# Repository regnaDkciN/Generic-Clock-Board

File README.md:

# Generic Clock Board

An ESP32 based PC board that is specifically designed to support electronic clocks.  Supports the following:
- Adafruit Huzzah32 - ESP32 Feather board for control.
- Optional Adafruit DS3231 Real Time Clock module.
- Optional 5 volt ULN2003 stepper motor driver with optional phase display LEDs (mainly intended for use with a 28BYJ-48 stepper motor).
- Optional home input for homing the stepper motor, if used.  Can be used for other purpose if home is not needed.
- RGB LED for status display.
- Pushbutton input for general clock use.
- Optional 2 auxiliary I/O which can be individually used as inputs or outputs as needed.
- All components are through hole for easy construction.
- Supporting Arduino IDE board driver written in C++.

The motivation for this board was gzumwalt's excellent Geneva Clock which was originally published on printables and cults3d:
[ https://www.printables.com/model/717033-geneva-clock](https://www.printables.com/model/717033-geneva-clock) and
 [https://cults3d.com/en/3d-model/home/geneva-clock](https://cults3d.com/en/3d-model/home/geneva-clock)

---
## Parts List
- 1 Generic Clock Board (files attached).
- 1 [Adafruit Huzzah32-ESP32](https://www.adafruit.com/product/3405).
- 1 **Optional** [Adafruit DS3231 Real Time Clock](https://www.adafruit.com/product/3013).  Used to provide battery backed time in case power is lost or an internet connection cannot be made.
- 1 **Optional**[Right Angle Tactile Pushbutton Switch](https://www.amazon.com/dp/B008DS16PO?psc=1&ref=ppx_yo2ov_dt_b_product_details).  Pushbutton for general clock use.
- 1 **Optional** [ULN2003 High Voltage Driver](https://www.amazon.com/ALLECIN-ULN2003-ULN2003APG-High-Voltage-High-Current/dp/B0CBM23ZJ3/ref=sr_1_5?sr=8-5).  Used to drive a 5 volt stepper motor.
- 1 **Optional** 10nf capacitor.  Used for ULN2003 bypass.
- 4 **Optional** LED (color as desired).  Used to display stepper motor phase selection, which might be useful for debugging stepper.  Otherwise, not really needed.
- 4 **Optional** 10K resistors.  Used only if the optional LEDs are included.
- 1 **Optional** [5 Pin JST XH Male Connector](https://www.amazon.com/dp/B09JP2D9BH?ref=ppx_yo2ov_dt_b_product_details).  Used to connect to the stepper motor, if used.
- 1 **Optional** [5mm RGB LED](https://www.amazon.com/EDGELEC-Tri-Color-Multicolor-Diffused-Resistors/dp/B077XGF3YR/ref=sr_1_5?sr=8-5).  To display general status if desired.
- 3 **Optional** 330 ohm resistors.  Supports RGB LED, if used.
- 1 **Optional** [2-pin JST male connector](https://www.amazon.com/daier-Micro-2-Pin-Connector-Female/dp/B01DUC1O68/ref=sr_1_9?sr=8-9).  Used for home sensor connector.
- 1 **Optional** [4-pin JST male connector](https://www.amazon.com/Sets-2-5-4-Connector-200mm-Female/dp/B01DUC1S14/ref=sr_1_4?sr=8-4).  For the optional auxiliary connector.

---

## Generic Clock Board Library

The included interface library provides convenient use of the basic elements of the board.  Interfaces exist for the stepper, LEDs, home sensor, and pushbutton switch.  The library consists of the following files:
- GenericClockBoard.h - Declares the GenericClockBoard class.
- GenericClockBoard.cpp - Contains the GenericClockBoard class method implementation.
- SerialDebugSetup.h - Selects compile time options for the SerialDebug library which is used to generate serial test and debug output for the library.

The GenericClockBoard library requires the following libraries to be installed in the Arduino IDE:
- [RGBLed Library](https://github.com/wilmouths/RGBLed): This library supports the board's RGB LEDs and provides dimming and color mixing support.
- [SerialDebug Library](https://github.com/JoaoLopesF/SerialDebug ): This library supports serial debugging and status display.

## StepperSpeed_t enum
This enum is used to select the speed profile that will be used for stepper movement via the Step() method.  Selections are:
- *__StepSlow__* - Will move the stepper at slow speed for the full duration of the move.
- *__StepAuto__* - Will make long moves use the fast speed with accel and decel at the beginning and end of the move.  Short moves will be done at slow speed.
- *__StepFast__* - Will move the stepper at fast speed for the full duration of the move.

## Generic Clock Board Library API
### Constructor
Constructs a class instance, initializes board hardware, and initializes instance variables.
#### Constructor Arguments:
 - *__rapidSecondsPerRev__*  - (uint32_t) Specifies the number of seconds it takes the stepper to make one full revolution of its output shaft.  For the 28BYJ-48 stepper motor, a good range is normally between 6 and 10 seconds.
- *__fullStepsPerRev__* - (uint32_t) Specifies the number of FULL steps per revolution of the stepper motor's output shaft.  For the   28BYJ-48 the value is 2048.
- *__stepperPinsReversed__* - (bool) Specifies the whether or not the stepper turns clockwise when a positive step value is commanded.  Set to 'true' if a positive step value causes counterclockwise movement.  Set to 'false' otherwise.
- *__stepperHalfStepping__* - (bool) Specifies whether half stepping is to be used.  If 'true', then half stepping is used, which will cause the number of steps per rev of the stepper to double.  For example, the 28BYJ-48 stepper will take 4096 steps per rev if this value is set to 'true'.  In most cases, use of half stepping is a good choice.
- *__homeNormallyOpen__* - (bool) Specifies the type of sensor used for homing the clock.  Set to 'true' for normally open  (N.O.) sensors.  Set to 'false' for normally closed (N.C.) sensors.

#### Constructor Example
```
// RAPID_SECONDS_PER_REV specifies the number of seconds it takes for the stepper
// motor to complete 1 full revolution at its maximum speed.  A good value for
// the 28BYJ-48 stepper motor is usually in the range of 6 to 10 seconds.
const uint32_t RAPID_SECONDS_PER_REV = 8;

// 28BYJ-48 has 2048 full steps per full rev of the output shaft (4096 half steps).
const uint32_t FULL_STEPS_PER_REV = 2048;

// This stepper needs to have the phases reversed.  Set to 'false' if stepper runs
// backwards.
const bool REVERSE_STEPPER = true;

// USE_HALF_STEPPING selects the use of half stepping of the stepper motor.
// Half stepping is recommended, and is specified by setting this constant to
// ture.  If full stepping is desired, set it to false.
const bool USE_HALF_STEPPING = true;

// The home sensor is normally open.  Set to false if normally closed.
const bool HOME_SWITCH_NORMALLY_OPEN = true;

GenericClockBoard gClock(RAPID_SECONDS_PER_REV, FULL_STEPS_PER_REV,  
                         REVERSE_STEPPER, USE_HALF_STEPPING, HOME_SWITCH_NORMALLY_OPEN);
```

### Step()
Step the stepper motor a specific number of steps in a specified direction at a specified speed.
#### Step() Arguments
- *__steps__* - (int32_t) Specifies the number of steps and direction that the motor will move.  A positive value will move the motor in the clockwise (CW) direction.  A negative value will move the motor in the counterclockwise (CCW) direction.
- *__speed__* - (StepperSpeed_t) Specifies the speed profile that will be used for the move.  StepSlow selects slow stepper speed.  StepAuto selects automatic stepper speed with accel and decel.  StepFast selects fast stepper speed.
#### Step() Example
```
	// Move the stepper 100 steps CW with the Auto profile.
	gClock.Step(100, StepAuto);
```
---
### IsHome()
Returns 'true' if the home sensor is active, based on the type of sensor (N.O. or N.C.) in use.  Returns 'false' otherwise.

#### IsHome() Example
```
	// Move the stepper slowly CW until home is found.
	while (!gClock.IsHome()
	{
		gClock.Step(1, StepSlow);
	}
```
---

### IsButtonPressed()
Returns 'true' if the board's pushbutton is active.  Returns 'false' otherwise.

#### IsButtonPressed() Example
```
	// Set the RGB LED to magenta if the button is pressed.
	if (gClock.IsButtonPressed())
	{
		gClock.RgbLed.brightness(RGBLed::MAGENTA, 2);
	}
```
---
### GenericClockBoard Public Data

#### RGB LED
The RGB LED is normally controlled via an instance of the RGBLed class that is created in the GenericClockBoard constructor.  The RGBLed instance is defined as:
```
    // RGBLed instance (public for easy access).
    static RGBLed RgbLed;
```
See the [RGBLed library documentation](https://github.com/wilmouths/RGBLed) for details on use.  An example of RgbLed is:
```
	// Set the RGB LED color to red with a brightness of 2.
	gClock.RgbLed.brightness(RGBLed::RED, 2);
```
The I/O pin assignments for the RGB LED are exposed as public constants, and may be used to control the LED if needed, but normally the RgbLed member should be used.  The LED pin assignments are defined as:
```
    static const uint8_t LED_RED_PIN   = 13;  // Red LED output pin assignment.
    static const uint8_t LED_GREEN_PIN = 12;  // Green LED output pin assignment.
    static const uint8_t LED_BLUE_PIN  = 27;  // Blue LED output pin assignment.
```
---

#### Auxiliary I/O Pin Assignments
The auxiliary I/O pin assignments are exposed for public use as follows:
```
    static const uint8_t AUX_1_PIN      = 15;  // Aux1 I/O pin assignment.
    static const uint8_t AUX_2_PIN      = 33;  // Aux2 I/O pin assignment.
```  
 These pins are not initialized or used in any way by the GenericClockBoard class, and can be used as desired.
 
---

#### Stepper Motor Direction Constants

The following constants may be used with the Step() method to assist in commanding the direction of stepper movement:
```
    static const int32_t STEP_CW        = 1;   // Clockwise specifier.
    static const int32_t STEP_CCW       = -1;  // Counterclockwise specifier.

```

An example of the use of these constants is:
```
	// Move 5 steps in the CCW direction.
	gClock.Step(STEP_CCW * 5, StepAuto);
```
---

### Private Constants
Several private constants may be of interest to users who do not want to use the provided GenericClockBoard code.  These constants identify the remainder of the I/O pins used by the board.
```
    // Stepper related constants.
    static const uint8_t PHASE_1_PIN = 19;
    static const uint8_t PHASE_2_PIN = 16;
    static const uint8_t PHASE_3_PIN = 17;
    static const uint8_t PHASE_4_PIN = 21;

    // I/O pin assignments.
    static const uint8_t HOME_PIN       = 32;   // Home input pin assignment.
    static const uint8_t PUSHBUTTON_PIN = 26;   // Pushbutton input pin assignment.

```
---

## General Notes
Interface to the ESP32 WiFi is left to the user.  The prototype code uses the 
[WiFiTimeManager library](https://github.com/regnaDkciN/WiFiTimeManager) for WiFi and DST management.  Similarly, interface to the DS3231 RTC is left to the user.  The prototype code uses the [DS323x_Generic Library](https://github.com/khoih-prog/DS323x_Generic) for RTC interface.

An example of using the full features of this board, including WiFi, DST management, RTC, RGB LEDs, and all other hardware can be found at [my GenevaClock git site](https://github.com/regnaDkciN/GenevaClock).

Next revision (if any) may include:
- Add an input for higher voltage ULN3003 feed for more capable stepper capability.
- Tie Home input and Selector Switch input to +5 volts instead of ground so that ESP32 internal pulldowns can be used to eliminate inversion in code.

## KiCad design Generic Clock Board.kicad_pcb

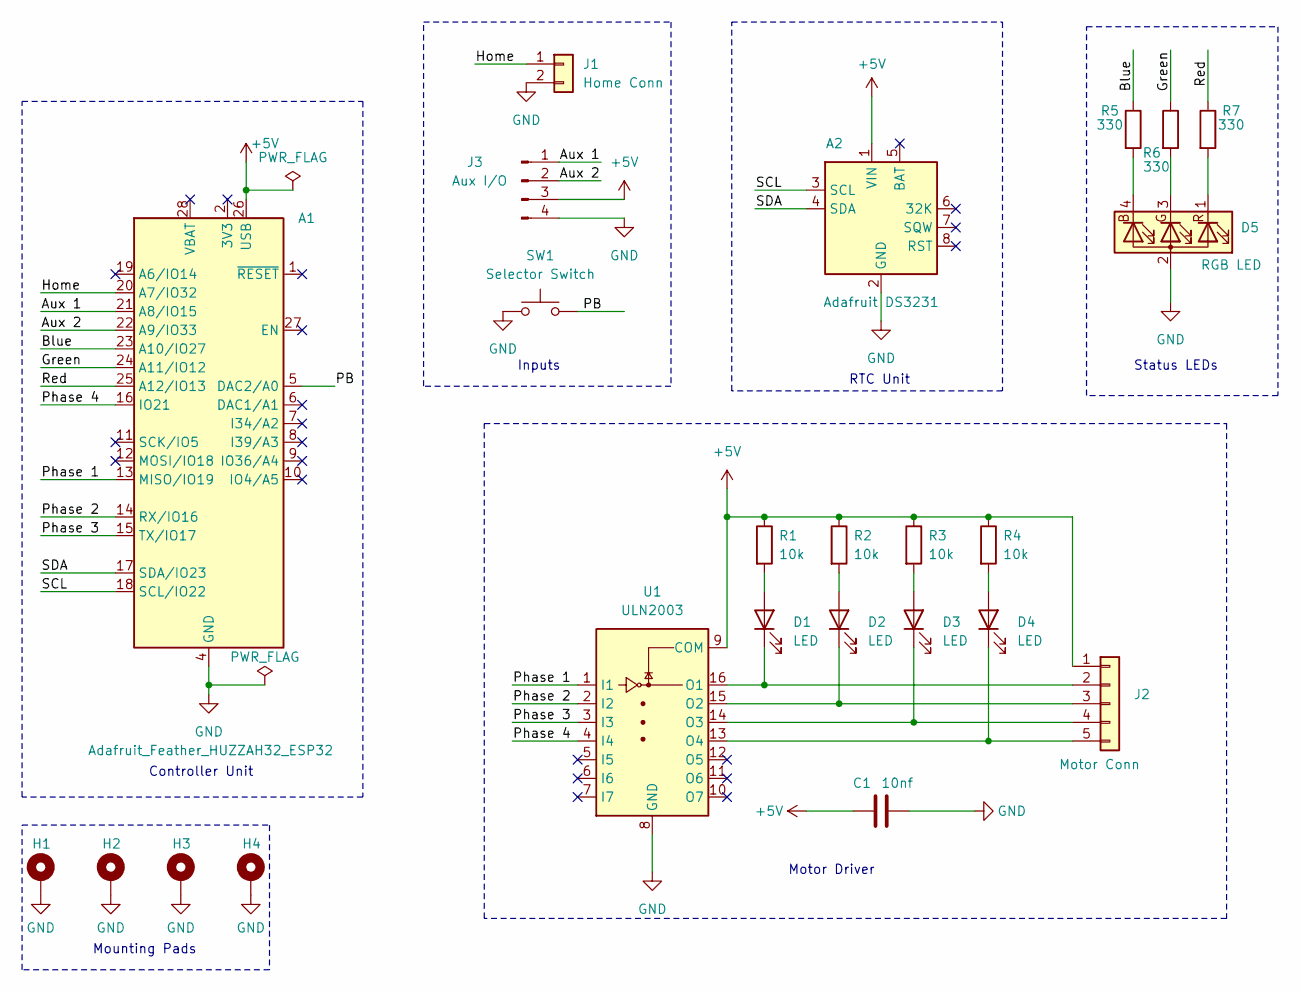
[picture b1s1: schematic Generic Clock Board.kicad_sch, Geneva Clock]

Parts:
A1: Adafruit_Feather_HUZZAH32_ESP32; Adafruit_Feather
A2: Adafruit DS3231; RTC_DS3231_Vertical
C1: 10nf; C_Disc_D3.8mm_W2.6mm_P2.50mm
D1, D2, D3, D4: LED; LED_D3.0mm
D5: RGB LED; LED_D5.0mm-4_RGB_Wide_Pins
H1, H2, H3, H4: MountingHole_Pad; MountingHole_2.7mm_M2.5_DIN965_Pad_TopBottom
J1: Home Conn; JST_EH_B2B-EH-A_1x02_P2.50mm_Vertical
J2: Motor Conn; JST_EH_B5B-EH-A_1x05_P2.50mm_Vertical
J3: Aux I/O; PinHeader_1x04_P2.54mm_Vertical
R1, R2, R3, R4: 10k; R_Axial_DIN0207_L6.3mm_D2.5mm_P2.54mm_Vertical
R5, R6, R7: 330; R_Axial_DIN0207_L6.3mm_D2.5mm_P7.62mm_Horizontal
SW1: Selector Switch; SW_SPST_Uxcell_Right_Angle
U1: ULN2003; DIP-16_W7.62mm

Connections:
+5V: A1.26 (USB), A2.1 (VIN), C1.1, J2.1, J3.3, R1.1, R2.1, R3.1, R4.1, U1.9 (COM)
/Aux 1: A1.21 (A8/IO15), J3.1
/Aux 2: A1.22 (A9/IO33), J3.2
/Blue: A1.23 (A10/IO27), R5.1
/Green: A1.24 (A11/IO12), R6.1
/Home: A1.20 (A7/IO32), J1.1
/PB: A1.5 (DAC2/A0), SW1.2
/Phase 1: A1.13 (MISO/IO19), U1.1 (I1)
/Phase 2: A1.14 (RX/IO16), U1.2 (I2)
/Phase 3: A1.15 (TX/IO17), U1.3 (I3)
/Phase 4: A1.16 (IO21), U1.4 (I4)
/Red: A1.25 (A12/IO13), R7.1
/SCL: A1.18 (SCL/IO22), A2.3 (SCL)
/SDA: A1.17 (SDA/IO23), A2.4 (SDA)
GND: A1.4 (GND), A2.2 (GND), C1.2, D5.2 (A), H1.1, H2.1, H3.1, H4.1, J1.2, J3.4, SW1.1, U1.8 (GND)
unnamed: D1.2 (A), R1.2
unnamed: D1.1 (K), J2.2, U1.16 (O1)
unnamed: D2.2 (A), R2.2
unnamed: D2.1 (K), J2.3, U1.15 (O2)
unnamed: D3.2 (A), R3.2
unnamed: D3.1 (K), J2.4, U1.14 (O3)
unnamed: D4.2 (A), R4.2
unnamed: D4.1 (K), J2.5, U1.13 (O4)
unnamed: D5.4 (BK), R5.2
unnamed: D5.3 (GK), R6.2
unnamed: D5.1 (RK), R7.2

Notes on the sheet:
Motor Driver
Status LEDs
Mounting Pads
Inputs
RTC Unit
Controller Unit

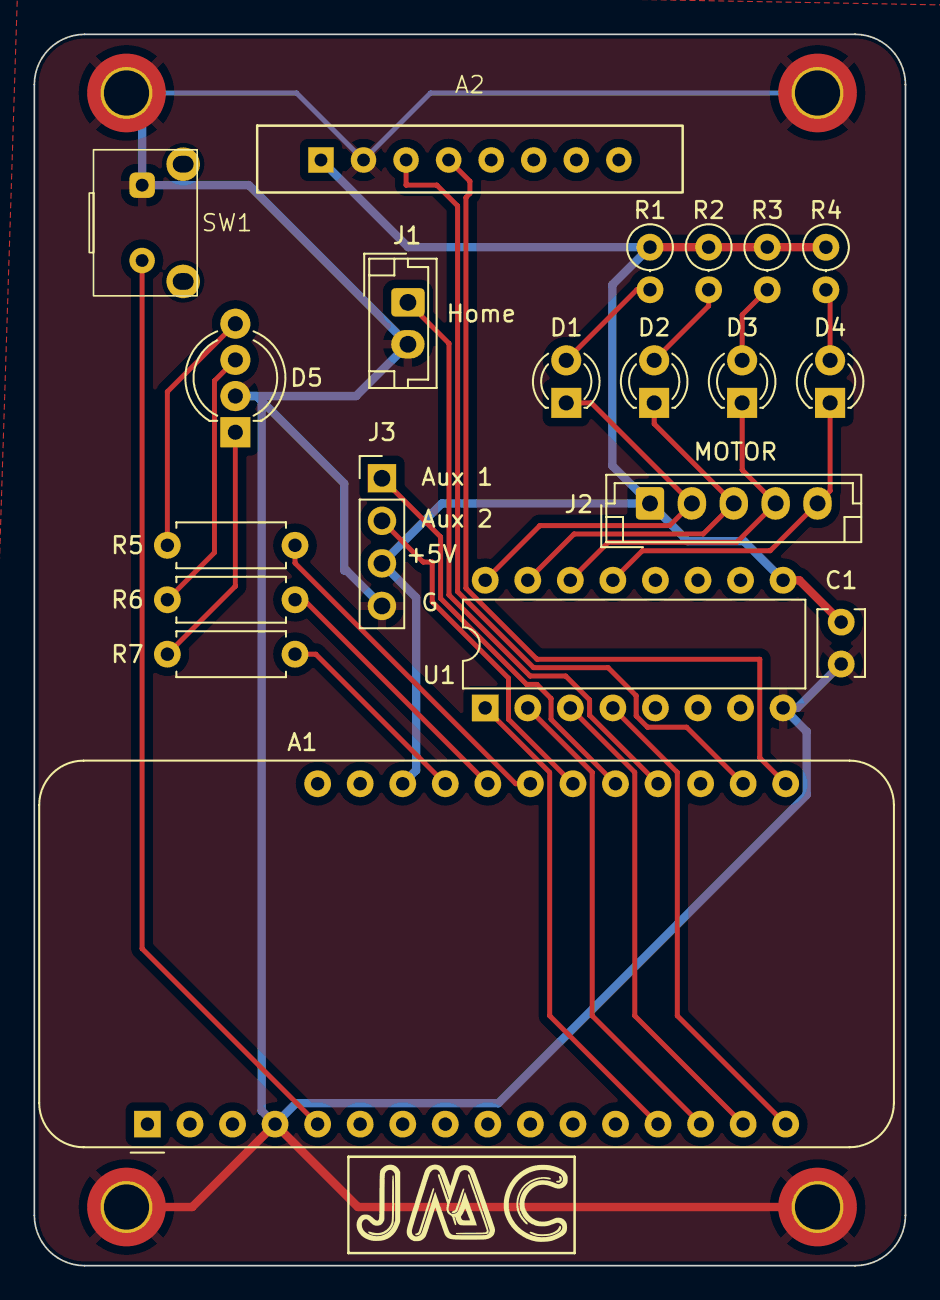
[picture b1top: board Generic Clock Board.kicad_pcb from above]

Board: 2 copper layers, 52.0 x 73.5 mm, 24 parts (0 on the bottom side), 26 nets.

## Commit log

2024-05-16 Original git release.
2024-05-17 Original release of README.md.
2024-05-17 Add .gitignore.
2024-05-18 Minor fix to readme.md.
2024-05-18 Added 10nf cap to parts list.
2024-06-01 Ignore a few more files.
